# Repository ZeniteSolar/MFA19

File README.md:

# MFP19
**M**ódulo da **F**onte **P**rincipal 2019  
Embarcação Guarapuvu II  
Equipe Zênite Solar  

### Sobre

Este módulo é responsável por fornecer uma tensao fixa e estavel de 18V para alimentaçao dos modulos que estao na rede CAN

#### Requisitos e Abordagens
1. Fornecer tensao estavel de 18V 
    - Manter a tensao estavel independente da carga (até 3A)
    - Baixo ripple
2. Ser robusta
    - Nao queimar por curto-circuito
    - Nao queimar por sobre temperatura
    - Nao queimar por sobre-carga
    - Resistencia por ruido eletromagnetico e eletrico causados pelos componentes do sistema (motor,MCC...)
3. Eficiencia energetica.
    -Conversor estatico DC/DC chaveado
4. Facilitar o diagnóstico
    - Utilizar LEDs
    
**CI Ultilizado: Conversor LMR16030**

[Datasheet]https://www.ti.com/lit/ds/symlink/lmr16030.pdf?ts=1596324314390&ref_url=https%253A%252F%252Fwww.google.com%252F

%20-%20lmr16030%20pdf.png?raw=true)

#### Projeto do Indutor

   -seleção do indutor de saida:

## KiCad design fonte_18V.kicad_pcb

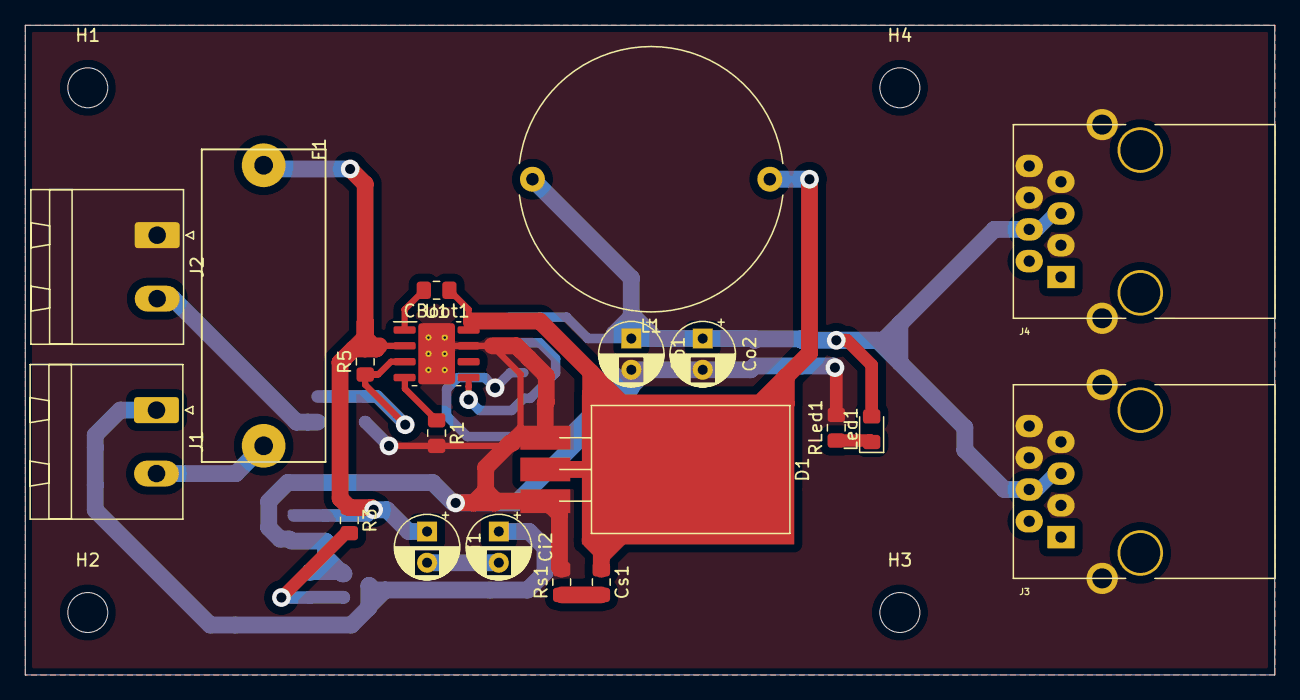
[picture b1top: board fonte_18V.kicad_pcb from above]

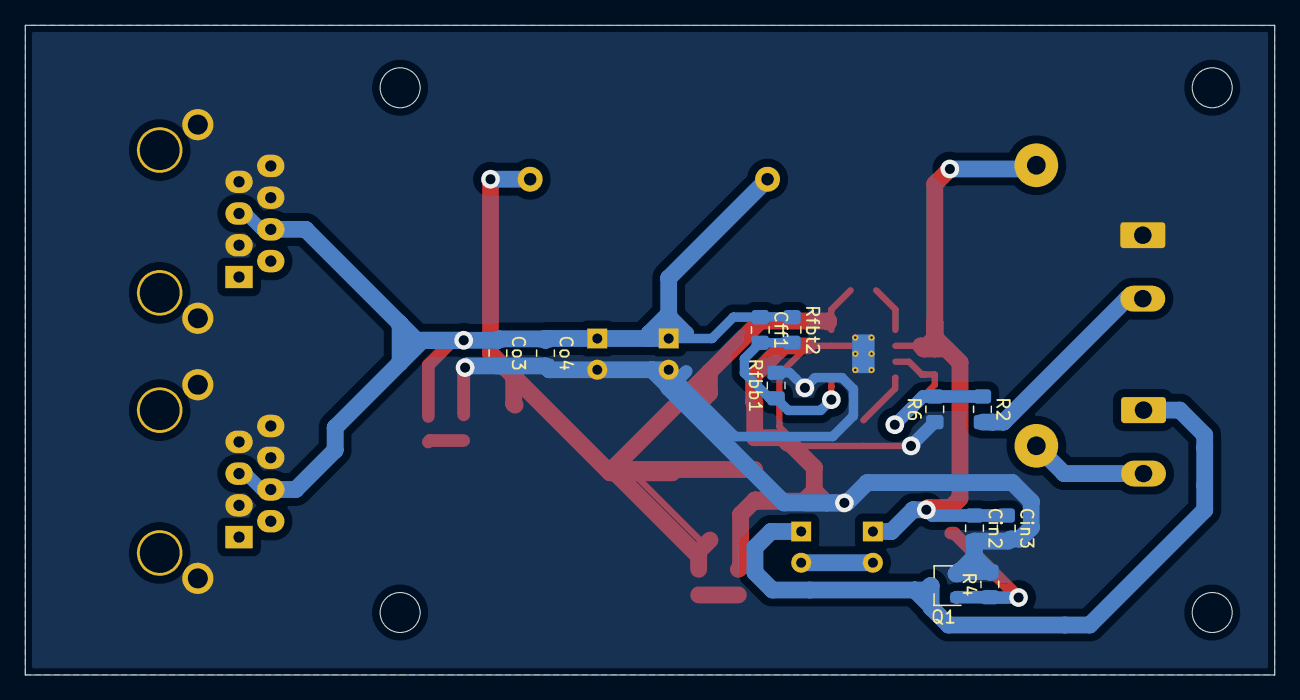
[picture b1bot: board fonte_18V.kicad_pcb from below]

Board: 2 copper layers, 100.0 x 52.0 mm, 35 parts (11 on the bottom side), 15 nets.

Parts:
CBoot1: 100nF; C_0805_2012Metric_Pad1.15x1.40mm_HandSolder
Cff1: na; C_0805_2012Metric_Pad1.15x1.40mm_HandSolder
Ci1, Ci2: 10u; CP_Radial_D5.0mm_P2.50mm
Cin2, Cin3: 100nF; C_0805_2012Metric_Pad1.15x1.40mm_HandSolder
Co1, Co2: 47u; CP_Radial_D5.0mm_P2.50mm
Co3: o.1u; C_0805_2012Metric_Pad1.15x1.40mm_HandSolder
Co4: 0.1u; C_0805_2012Metric_Pad1.15x1.40mm_HandSolder
Cs1: 100n; C_0805_2012Metric_Pad1.15x1.40mm_HandSolder
D1: MBR20200CTG; TO-220-3_Horizontal_TabDown_SMD
F1: 2A; Fuse_Holder_5x20
H1, H2, H3, H4: MountingHole; MountingHole_3.2mm_M3
J1, J2: MSTBA; PhoenixContact_MSTBA_2,5_2-G-5,08_1x02_P5.08mm_Horizontal
J3, J4: RJ45_Shielded; RJ45_YH59_01
L1: 100uH; L_Radial_D21.0mm_P19.00mm
Led1: LED; LED_0805_2012Metric_Pad1.15x1.40mm_HandSolder
Q1: Si2308CDS; SOT-23
R1: 47k; R_0805_2012Metric_Pad1.15x1.40mm_HandSolder
R2: 100; R_0805_2012Metric_Pad1.15x1.40mm_HandSolder
R3: 220K; R_0805_2012Metric_Pad1.15x1.40mm_HandSolder
R4: 100K; R_0805_2012Metric_Pad1.15x1.40mm_HandSolder
R5: 10K; R_0805_2012Metric_Pad1.15x1.40mm_HandSolder
R6: NA; R_0805_2012Metric_Pad1.15x1.40mm_HandSolder
RLed1: 1k5; R_0805_2012Metric_Pad1.15x1.40mm_HandSolder
Rfbb1: 8k2; R_0805_2012Metric_Pad1.15x1.40mm_HandSolder
Rfbt2: 230k; R_0805_2012Metric_Pad1.15x1.40mm_HandSolder
Rs1: 2k2; R_0805_2012Metric_Pad1.15x1.40mm_HandSolder
U1: LMR16030; Texas_R-PDSO-G8_EP2.95x4.9mm_Mask2.4x3.1mm_ThermalVias

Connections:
/CAN_18V: Cff1.1, Co1.1, Co2.1, Co3.1, Co4.1, J3.4, J3.5, J4.4, J4.5, L1.2, Led1.2, Rfbt2.1
/Feedback: Cff1.2, Rfbb1.1, Rfbt2.2, U1.5
/snbr: Cs1.2, Rs1.1
GND: Cin2.2, Cin3.2, Co1.2, Co2.2, Co3.2, Co4.2, D1.1, D1.3, J2.1, J3.3, J3.6, J3.7, J3.8, J3.9, J4.3, J4.6, J4.7, J4.8, J4.9, Q1.2, R1.2, R4.2, R6.1, RLed1.2, Rfbb1.2, Rs1.2, U1.7, U1.9
unnamed: CBoot1.1, Cs1.1, D1.2, L1.1, U1.8
unnamed: CBoot1.2, U1.1
unnamed: Ci1.1, Cin2.1, Cin3.1, F1.1, R3.1, R5.2, U1.2
unnamed: Ci1.2, Ci2.2
unnamed: Ci2.1, J1.1, Q1.3
unnamed: F1.2, J1.2
unnamed: J2.2, R2.2
unnamed: Led1.1, RLed1.1
unnamed: Q1.1, R3.2, R4.1
unnamed: R1.1, U1.4
unnamed: R2.1, R5.1, R6.2, U1.3

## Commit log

2019-03-28 Esquemático para fonte principal de 18V.
2019-04-23 upload
2019-04-23 update 2
2019-09-03 conectores e proteção de polaridade
2019-09-03 schematico centralizado
2019-09-06 snuber e capacitores adicionados. valores de capacitores alterados
2019-10-01 mudança de capacitores de entrada nomeou os componentes do circuito footprints alterados erc rodado
2019-10-29 Conectores rj45 adicionados, trilhas melhoradas, acabamentos gerais
2019-11-02 atualizado
2019-11-02 Pads reforçados, algumas pequenas correções de regras
2020-07-13 export 3D and layout images
2020-07-29 Create LMR16030sch
2020-09-03 Create LICENSE
